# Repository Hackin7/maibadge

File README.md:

# maibadge
maimai badge project. PCB badges with maimai themes

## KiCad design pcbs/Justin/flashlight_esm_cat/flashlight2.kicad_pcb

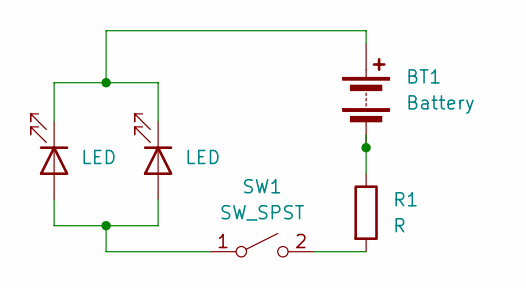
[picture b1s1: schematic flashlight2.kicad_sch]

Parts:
BT1: Battery; BatteryHolder_Keystone_106_1x20mm
D1, D2: LED; LED_D3.0mm
R1: R; R_0805_2012Metric_Pad1.20x1.40mm_HandSolder
SW1: SW_SPST; SS12D00

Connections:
unnamed: BT1.1 (+), D1.1 (K), D2.1 (K)
unnamed: BT1.2 (-), R1.1
unnamed: D1.2 (A), D2.2 (A), SW1.1 (A)
unnamed: R1.2, SW1.2 (B)

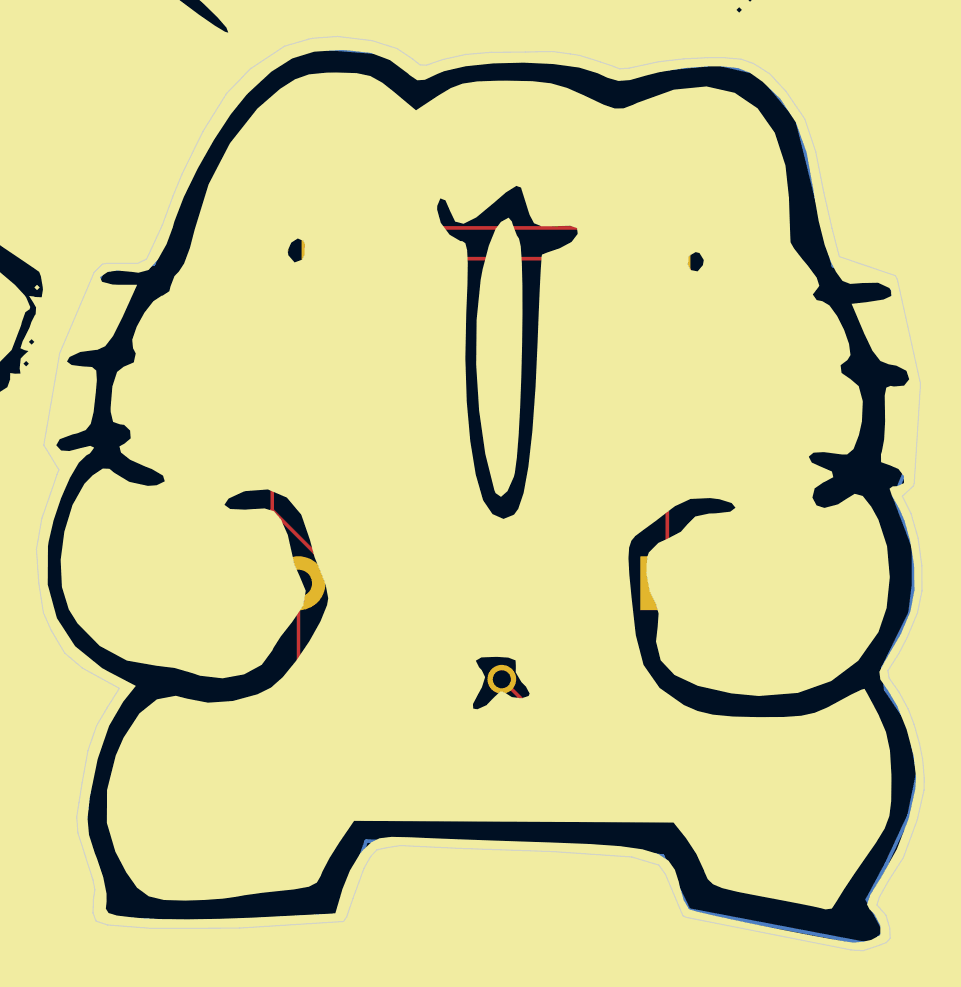
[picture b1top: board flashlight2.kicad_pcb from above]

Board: 2 copper layers, 49.3 x 50.8 mm, 5 parts (1 on the bottom side), 4 nets.

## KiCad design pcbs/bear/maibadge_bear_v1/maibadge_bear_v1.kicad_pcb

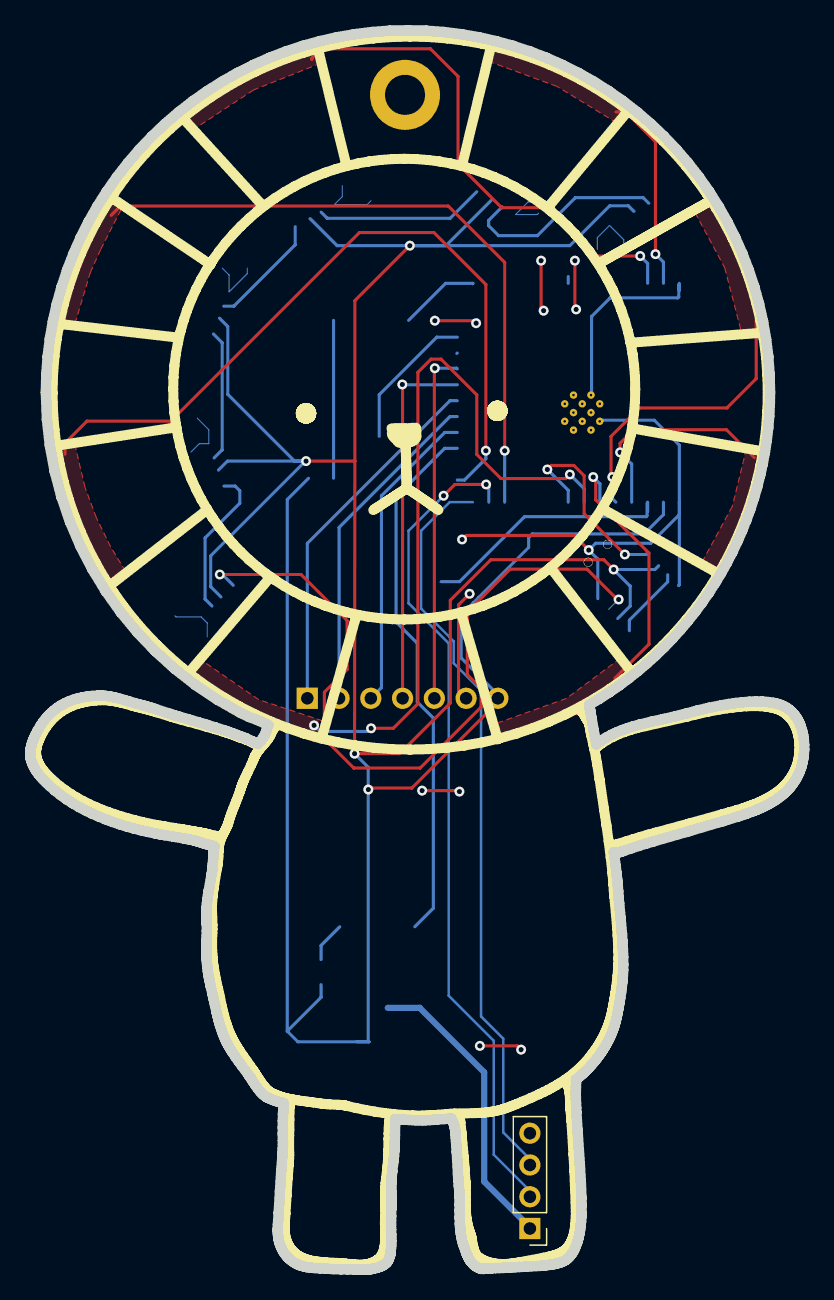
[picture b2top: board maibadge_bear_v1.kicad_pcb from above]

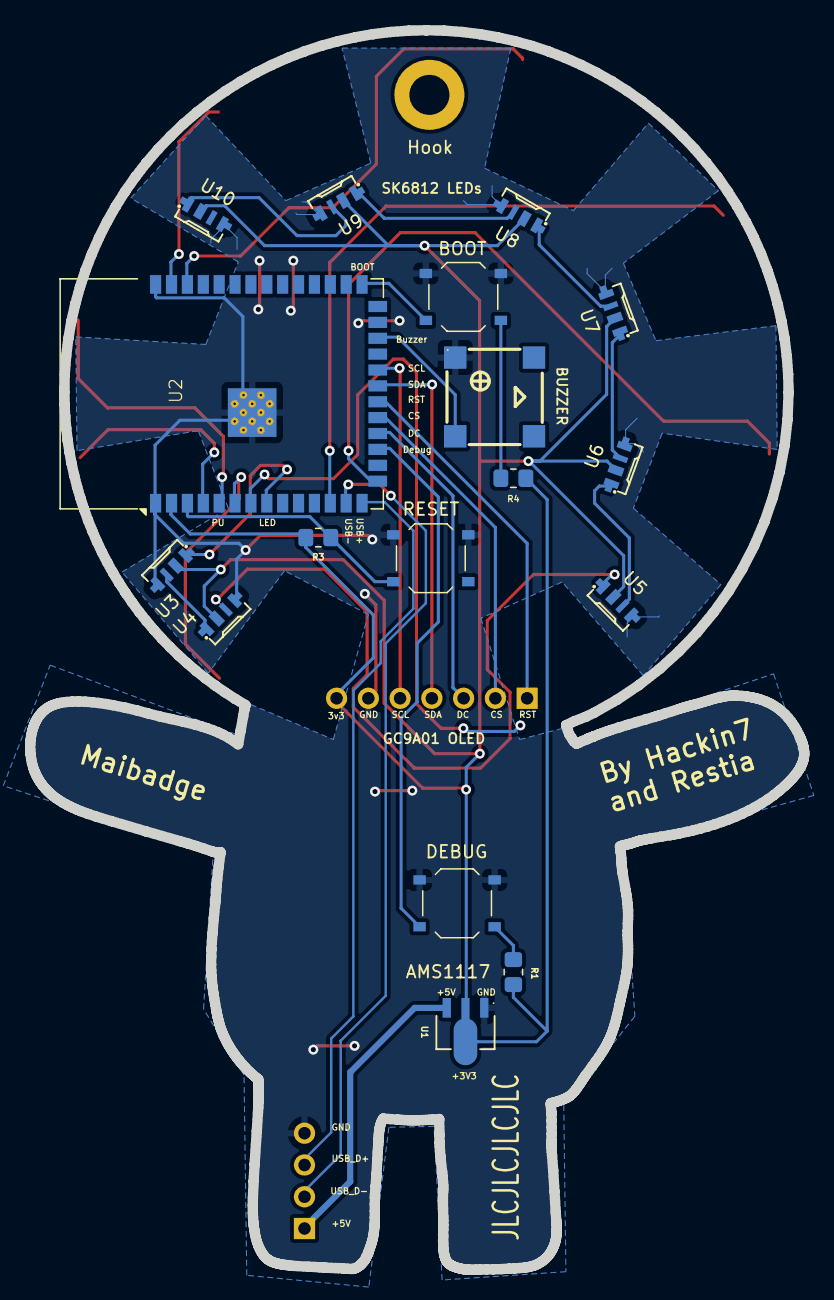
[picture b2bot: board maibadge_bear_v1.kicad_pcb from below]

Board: 2 copper layers, 61.9 x 99.1 mm, 20 parts (18 on the bottom side), 22 nets.

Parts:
BOOT1: SW_Push; SW_Push_1P1T_XKB_TS-1187A
DEBUG1: SW_Push; SW_Push_1P1T_XKB_TS-1187A
GC9A1: CG9A01; GC9A01
Hook: MountingHole_3.2mm_M3_DIN965_Pad
J1: Conn_01x04_Socket; PinHeader_1x04_P2.54mm_Vertical
R1, R3, R4: R; R_0805_2012Metric_Pad1.20x1.40mm_HandSolder
RESET1: SW_Push; SW_Push_1P1T_XKB_TS-1187A
U1: AMS1117-3.3; SOT-89-3_L4.5-W2.5-P1.50-LS4.2-BR
U2: ESP32-S3-WROOM-1; esp32-s3-wroom-1-without-keep-out-zone
U3, U4, U5, U6, U7, U8, U9, U10: SK6812SIDE-A-RVS; LED-SMD_4P-L4.0-W1.6-L
U13: FUET-7525-3_6V; BUZ-SMD_4P-L7.5-W7.5-BR

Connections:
+3.3V: GC9A1.7 (VCC), R1.1, R3.1, R4.1, U1.2 (VOUT), U2.2 (3V3), U3.2 (VDD), U4.2 (VDD), U5.2 (VDD), U6.2 (VDD), U7.2 (VDD), U8.2 (VDD), U9.2 (VDD), U10.2 (VDD)
+5V: J1.1, U1.3 (VIN)
/CHIP_PU: R3.2, RESET1.2, U2.3 (EN)
/GPIO0_BOOT: BOOT1.2, R4.2, U2.27 (IO0)
/OLED_CS: GC9A1.2 (CS), U2.19 (IO11)
/OLED_DC: GC9A1.3 (DC), U2.18 (IO10)
/OLED_RST: GC9A1.1 (RST), U2.20 (IO12)
/OLED_SCL: GC9A1.5 (SCL), U2.22 (IO14)
/OLED_SDA: GC9A1.4 (SDA), U2.21 (IO13)
/USB_D+: J1.3, U2.14 (IO20)
/USB_D-: J1.2, U2.13 (IO19)
/button 1: DEBUG1.2, R1.2, U2.17 (IO9)
/buzzer: U2.24 (IO47), U13.2
/main led DIN: U2.8 (IO15), U3.1 (DIN)
GND: BOOT1.1, DEBUG1.1, GC9A1.6 (GND), J1.4, RESET1.1, U1.1 (GND/ADJ), U2.1 (GND), U2.40 (GND), U2.41 (GND), U3.4 (GND), U4.4 (GND), U5.4 (GND), U6.4 (GND), U7.4 (GND), U8.4 (GND), U9.4 (GND), U10.4 (GND), U13.1
unnamed: U3.3 (DOUT), U4.1 (DIN)
unnamed: U4.3 (DOUT), U5.1 (DIN)
unnamed: U5.3 (DOUT), U6.1 (DIN)
unnamed: U6.3 (DOUT), U7.1 (DIN)
unnamed: U7.3 (DOUT), U8.1 (DIN)
unnamed: U8.3 (DOUT), U9.1 (DIN)
unnamed: U9.3 (DOUT), U10.1 (DIN)

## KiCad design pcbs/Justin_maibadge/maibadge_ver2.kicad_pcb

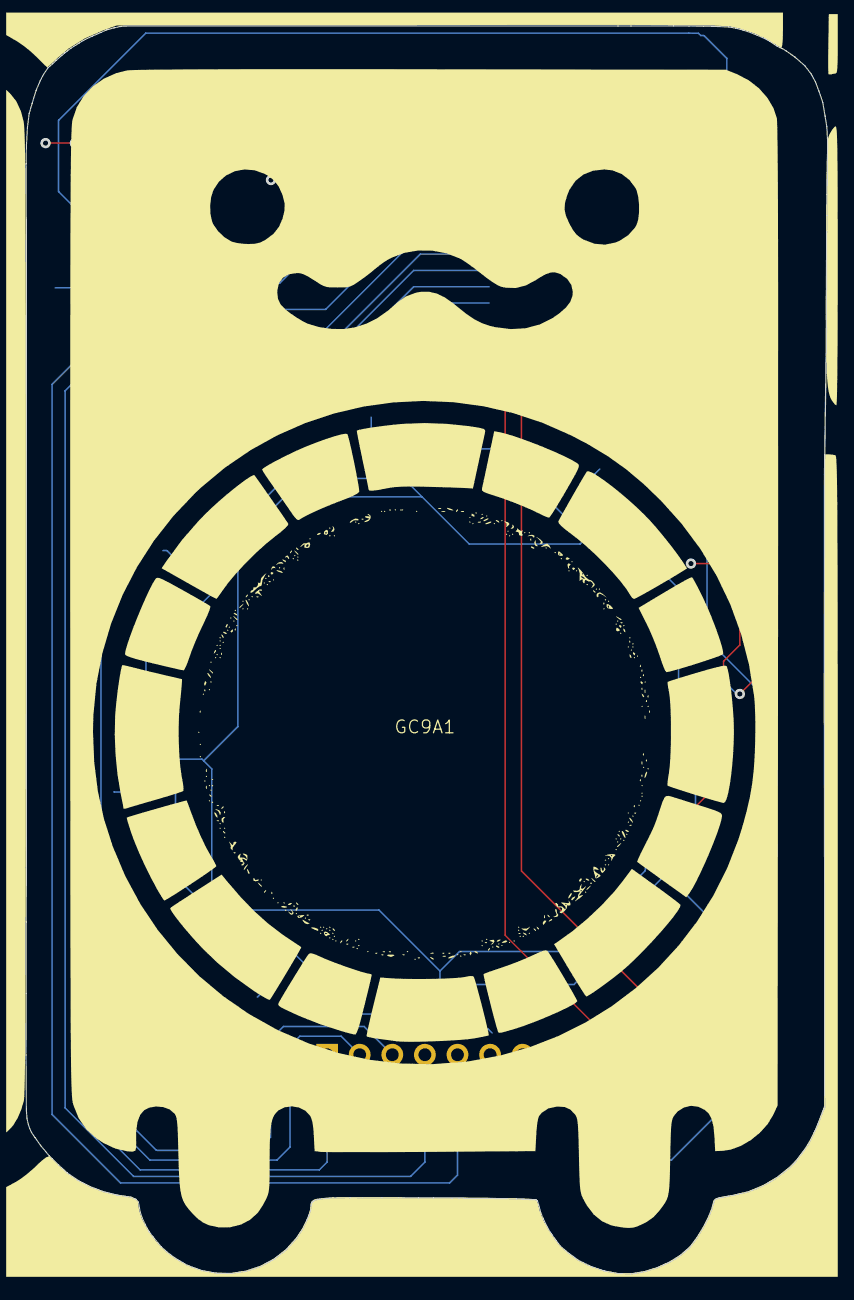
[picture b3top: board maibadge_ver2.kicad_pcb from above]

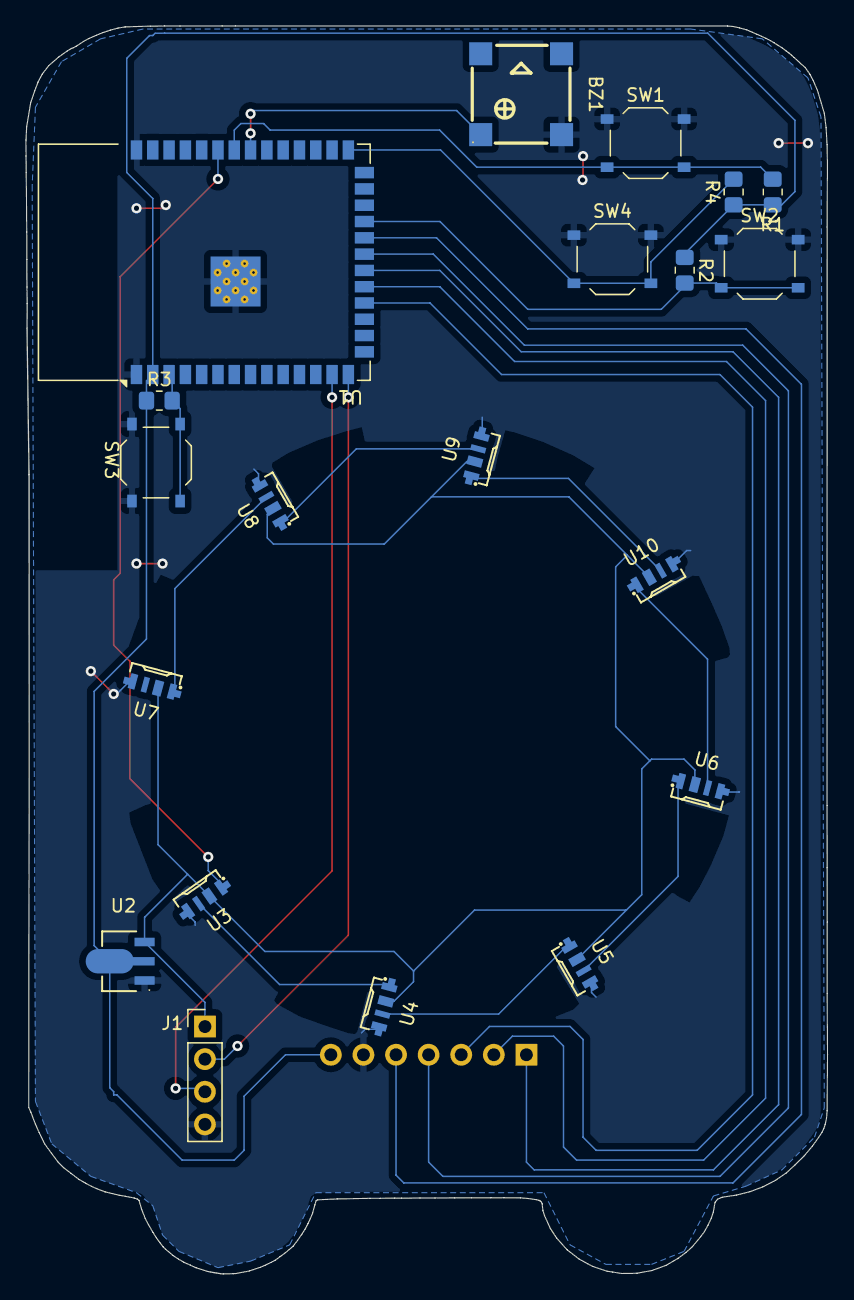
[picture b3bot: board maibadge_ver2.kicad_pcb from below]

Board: 2 copper layers, 62.4 x 97.2 mm, 21 parts (20 on the bottom side), 23 nets.

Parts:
BZ1: Buzzer; BUZ-SMD_4P-L7.5-W7.5-BR
GC9A1: CG9A01; GC9A01
J1: Conn_01x04_Socket; PinHeader_1x04_P2.54mm_Vertical
R1, R2, R3, R4: R; R_0805_2012Metric_Pad1.20x1.40mm_HandSolder
SW1, SW2, SW3, SW4: SW_Push; SW_Push_1P1T_XKB_TS-1187A
U1: ESP32-S3-WROOM-1
U2: AMS1117-3.3; SOT-89-3_L4.5-W2.5-P1.50-LS4.2-BR
U3, U4, U5, U6, U7, U8, U9, U10: SK6812SIDE-A-RVS; LED-SMD_4P-L4.0-W1.6-L

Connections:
+3.3V: GC9A1.7 (VCC), R1.1, R2.1, R3.1, R4.1, U1.2 (3V3), U2.2 (VOUT)
+5V: J1.1, U2.3 (VIN), U3.2 (VDD), U4.2 (VDD), U5.2 (VDD), U6.2 (VDD), U7.2 (VDD), U8.2 (VDD), U9.2 (VDD), U10.2 (VDD)
/CHIP_PU: R3.2, SW3.2, U1.3 (EN)
/GPIO0_BOOT: R4.2, SW4.2, U1.27 (IO0)
/OLED_CS: GC9A1.2 (CS), U1.19 (IO11)
/OLED_DC: GC9A1.3 (DC), U1.18 (IO10)
/OLED_RST: GC9A1.1 (RST), U1.20 (IO12)
/OLED_SCL: GC9A1.5 (SCL), U1.22 (IO14)
/OLED_SDA: GC9A1.4 (SDA), U1.21 (IO13)
/USB_D+: J1.2, U1.14 (IO20)
/USB_D-: J1.3, U1.13 (IO19)
/button 1: R2.2, SW2.2, U1.23 (IO21)
/button 2: R1.2, SW1.2, U1.34 (IO41)
/buzzer: BZ1.1 (+), U1.33 (IO40)
/main led DIN: U1.35 (IO42), U3.1 (DIN)
GND: BZ1.2 (-), GC9A1.6 (GND), J1.4, SW1.1, SW2.1, SW3.1, SW4.1, U1.1 (GND), U1.40 (GND), U1.41 (GND), U2.1 (GND/ADJ), U3.4 (GND), U4.4 (GND), U5.4 (GND), U6.4 (GND), U7.4 (GND), U8.4 (GND), U9.4 (GND), U10.4 (GND)
unnamed: U3.3 (DOUT), U4.1 (DIN)
unnamed: U4.3 (DOUT), U5.1 (DIN)
unnamed: U5.3 (DOUT), U6.1 (DIN)
unnamed: U7.1 (DIN), U8.3 (DOUT)
unnamed: U8.1 (DIN), U9.3 (DOUT)
unnamed: U6.3 (DOUT), U10.1 (DIN)
unnamed: U9.1 (DIN), U10.3 (DOUT)

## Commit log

2024-08-18 feat: initial bear pcb
2024-08-18 feat: component placement adjustments
2024-08-19 changed OLED routing to HSPI, changed footprint for buttons and resistors, finished routing, ensured no components behind the 8 buttons
2024-08-21 files for hardware
2024-08-26 pcb routing fixed
2024-09-04 order 1
2024-09-18 added leds and mpr121 for pcb
2024-09-20 code for displaying stuff added
2024-09-21 feat: updated code
2024-09-24 code update
2024-09-24 change folder name
2024-09-24 maigame
2024-09-25 flashlight
2024-09-26 prototype 2 done
2024-10-20 feat: copy 1
2024-10-26 minor edits to touch layout
2024-10-26 minor edits
2024-10-26 chore: cleanup
2024-10-28 chore: refactoring & organisation in progress
2024-10-28 prototype 2 rehaul finished
2024-11-16 feat: Simple Template
2024-11-17 feat: menu_images
2024-11-17 feat: menu graphic
2024-11-17 feat: touch
2024-11-17 feat: simple menu
2024-11-17 feat: buzz + animate
2024-11-18 final changes
2024-11-18 feat: maigame works yay
2024-11-24 feat: update images
2024-11-24 feat: face update
2024-11-24 feat: face autoload
2024-11-25 button memory but failed maigame_2
2024-11-26 completed maigame_2
2024-12-01 feat: images
2024-12-19 feat: power fixes and touchpad routing
2024-12-19 feat: routing cleanup for face
2024-12-19 feat: author + keychain hole
2024-12-19 feat: renaming labels and further touchups
2024-12-19 feat: labelling components
2024-12-19 feat: component labelling and hook
2024-12-19 feat: minor edits again
2024-12-19 feat: shrink pcb size lol
2024-12-19 feat: clean up silkscreen
2024-12-19 feat: production ready???
2025-01-23 Create a
2025-02-21 feat: added graphics
2025-03-01 Added website files to pcbs/Justin/website
